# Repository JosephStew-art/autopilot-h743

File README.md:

STM32H743 autopilot board designed in KiCad. V2 routing is complete silkscreen cleanup remains.

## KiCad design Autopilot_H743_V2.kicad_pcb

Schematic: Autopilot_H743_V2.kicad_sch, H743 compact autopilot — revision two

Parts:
C1, C2: 33pF; Capacitor_SMD__C_0603_1608Metric; Rating 33pF / 100V C0G; MPN GCM1885C2A330JA16D; LCSC C126578
C3, C4, C8, C9, C10, C11, C12, C13, C14, C15, C16, C26, C29, C30, C32, C33, C35, C36, C39, C42, C43, C44, C45, C46: 100nF; C_0402_1005Metric; Rating 100nF / 16V X7R; MPN CL05B104KO5NNNC; LCSC C1525
C5, C6, C22, C34: 22uF; Capacitor_SMD__C_0805_2012Metric; Rating 22uF / 25V X5R; MPN CL21A226MAQNNNE; LCSC C45783
C7, C21, C38, C41: 10uF; Capacitor_SMD__C_0805_2012Metric; Rating 10uF / 35V X5R; MPN GRM21BR6YA106KE43L; LCSC C162422
C17, C28: 4.7uF; Capacitor_SMD__C_0603_1608Metric; Rating 4.7uF / 16V X5R; MPN CL10A475KO8NNNC; LCSC C19666
C18, C23, C24, C25, C27, C31, C37, C40: 1uF; Capacitor_SMD__C_0603_1608Metric; Rating 1uF / 50V X5R; MPN CL10A105KB8NNNC; LCSC C15849
C19, C20: 2.2uF; Capacitor_SMD__C_0603_1608Metric; Rating 2.2uF / 16V X5R; MPN CL10A225KO8NNNC; LCSC C23630
C47: 47uF; Capacitor_SMD__C_1206_3216Metric; Rating 47uF / 10V X5R; DC-bias derating applies; MPN CL31A476MPHNNNE; LCSC C96123
D1: RED; LED_SMD__LED_0603_1608Metric; Rating RED / status; MPN KT-0603R; LCSC C2286
F1: 1.5A hold; Fuse__Fuse_1812_4532Metric; Rating 1.5A hold / 16V; MPN SMD1812P150TF/16; LCSC C20810
J2: 5V BEC INPUT PADS; PowerInput_2Pad_4x4mm_P7mm; Rating Regulated 4.75-5.25 V; shared avionics 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
J3: TYPE-C-31-M-12; Connector_USB__USB_C_Receptacle_HRO_TYPE-C-31-M-12; Rating TYPE-C-31-M-12; MPN TYPE-C-31-M-12; LCSC C165948
J4: TF-01A / microSD; TF-01A; Rating TF-01A / microSD; MPN TF-01A; LCSC C91145
L1: 4.7uH; SRN6045; Rating 4.7uH / Irms3A / Isat4A; MPN SRN6045-4R7Y; LCSC C780210
Q1: AO3401A; Package_TO_SOT_SMD__SOT-23; Rating AO3401A; MPN AO3401A; LCSC C15127
Q2: MMBT3906 PNP; Package_TO_SOT_SMD__SOT-23; Rating MMBT3906 PNP; MPN MMBT3906 2A(RANGE:100-300); LCSC C2143
Q3: MMBT2222A NPN; Package_TO_SOT_SMD__SOT-23; Rating MMBT2222A NPN; MPN MMBT2222A 1P; LCSC C8512
R1, R2, R8, R12, R13, R17, R22, R23, R24, R38, R52, R59, R60, R61: 10k; R_0402_1005Metric; Rating 10k / 1% / 62.5mW; MPN 0402WGF1002TCE; LCSC C25744
R3, R57, R58: 1k; R_0402_1005Metric; Rating 1k / 1% / 62.5mW; MPN 0402WGF1001TCE; LCSC C11702
R4, R5, R14, R16, R20, R21, R62, R63, R64, R65, R66, R67, R68, R69, R71, R73, R75, R77, R79, R81, R83, R85: 100k; R_0402_1005Metric; Rating 100k / 1% / 62.5mW; MPN 0402WGF1003TCE; LCSC C25741
R6: 24k; R_0402_1005Metric; Rating 24k / 1% / 62.5mW; MPN 0402WGF2402TCE; LCSC C25769
R7: 470; R_0402_1005Metric; Rating 470 / 1% / 62.5mW; MPN 0402WGF4700TCE; LCSC C25117
R9, R10, R11: 300k; R_0402_1005Metric; Rating 300k / 1% / 62.5mW; MPN 0402WGF3003TCE; LCSC C25774
R15: 20k; R_0402_1005Metric; Rating 20k / 1% / 62.5mW; MPN 0402WGF2002TCE; LCSC C25765
R18, R19, R27, R28, R29, R30, R31, R32, R39, R40, R41, R42, R43, R44, R45, R46, R47, R48, R49, R50, R53, R54, R70, R72, R74, R76, R78, R80, R82, R84: 33; R_0402_1005Metric; Rating 33 / 1% / 62.5mW; MPN 0402WGF330JTCE; LCSC C25105
R25, R26, R55, R56: 4.7k; R_0402_1005Metric; Rating 4.7k / 1% / 62.5mW; MPN 0402WGF4701TCE; LCSC C25900
R33, R34, R35, R36, R37, R51: 49.9k; R_0402_1005Metric; Rating 49.9k / 1% / 62.5mW; MPN 0402WGF4992TCE; LCSC C25897
SW1: RESET; SW_TS-1088-AR02016; Rating RESET; MPN TS-1088-AR02016; LCSC C720477
SW2: BOOT; SW_TS-1088-AR02016; Rating BOOT; MPN TS-1088-AR02016; LCSC C720477
TP1, TP29: V3V3_CORE; SolderPad_D1.5mm; Rating V3V3_CORE
TP2: SWDIO; SolderPad_D1.2mm; Rating SWDIO
TP3: SWCLK; SolderPad_D1.2mm; Rating SWCLK
TP4, TP8, TP12, TP16, TP20, TP24, TP28, TP32, TP33, TP36, TP37, TP40, TP43, TP46, TP49, TP52, TP55, TP58: GND; SolderPad_D1.5mm; Rating GND
TP5, TP9, TP13, TP17, TP21, TP25: V5_PERIPH; SolderPad_D1.5mm; Rating V5_PERIPH
TP6: UART7_TX_EXT; SolderPad_D1.2mm; Rating UART7_TX_EXT
TP7: UART7_RX_EXT; SolderPad_D1.2mm; Rating UART7_RX_EXT
TP10: USART1_TX_EXT; SolderPad_D1.2mm; Rating USART1_TX_EXT
TP11: USART1_RX_EXT; SolderPad_D1.2mm; Rating USART1_RX_EXT
TP14: USART2_TX_EXT; SolderPad_D1.2mm; Rating USART2_TX_EXT
TP15: USART2_RX_EXT; SolderPad_D1.2mm; Rating USART2_RX_EXT
TP18: USART3_TX_EXT; SolderPad_D1.2mm; Rating USART3_TX_EXT
TP19: USART3_RX_EXT; SolderPad_D1.2mm; Rating USART3_RX_EXT
TP22: UART8_TX_EXT; SolderPad_D1.2mm; Rating UART8_TX_EXT
TP23: UART8_RX_EXT; SolderPad_D1.2mm; Rating UART8_RX_EXT
TP26: USART6_TX_EXT; SolderPad_D1.2mm; Rating USART6_TX_EXT
TP27: USART6_RX_EXT; SolderPad_D1.2mm; Rating USART6_RX_EXT
TP30: I2C1_SCL_EXT; SolderPad_D1.2mm; Rating I2C1_SCL_EXT
TP31: I2C1_SDA_EXT; SolderPad_D1.2mm; Rating I2C1_SDA_EXT
TP34: BATT_V_IN; SolderPad_D1.2mm; Rating BATT_V_IN
TP35: BATT_I_IN; SolderPad_D1.2mm; Rating BATT_I_IN
TP38, TP41, TP44, TP47, TP50, TP53, TP56, TP59: V5_MAIN_IN; SolderPad_D1.5mm; Rating V5_MAIN_IN
TP39: PWM1_OUT; SolderPad_D1.2mm; Rating PWM1_OUT
TP42: PWM2_OUT; SolderPad_D1.2mm; Rating PWM2_OUT
TP45: PWM3_OUT; SolderPad_D1.2mm; Rating PWM3_OUT
TP48: PWM4_OUT; SolderPad_D1.2mm; Rating PWM4_OUT
TP51: PWM5_OUT; SolderPad_D1.2mm; Rating PWM5_OUT
TP54: PWM6_OUT; SolderPad_D1.2mm; Rating PWM6_OUT
TP57: PWM7_OUT; SolderPad_D1.2mm; Rating PWM7_OUT
TP60: PWM8_OUT; SolderPad_D1.2mm; Rating PWM8_OUT
U1: STM32H743VIT6; Package_QFP__LQFP-100_14x14mm_P0.5mm; Rating STM32H743VIT6; MPN STM32H743VIT6; LCSC C114409
U2: AP63203WU-7; Package_TO_SOT_SMD__TSOT-23-6; Rating AP63203WU-7; MPN AP63203WU-7; LCSC C780769
U3: TPS2113APWR; Package_SO__TSSOP-8_4.4x3mm_P0.65mm; Rating TPS2113APWR; MPN TPS2113APWR; LCSC C130052
U4, U9: TPS7A2033PDBVR; Package_TO_SOT_SMD__SOT-23-5; Rating TPS7A2033PDBVR; MPN TPS7A2033PDBVR; LCSC C2862740
U5: TUSB320LIRWBR; Package_DFN_QFN__Texas_X2QFN-12_1.6x1.6mm_P0.4mm; Rating TUSB320LIRWBR; MPN TUSB320LIRWBR; LCSC C2836598
U6, U19: TPS2553DBVR; Package_TO_SOT_SMD__SOT-23-6; Rating TPS2553DBVR; MPN TPS2553DBVR; LCSC C55266
U7, U8, U13, U14, U15, U16, U17, U18, U20: USBLC6-2SC6; Package_TO_SOT_SMD__SOT-23-6; Rating USBLC6-2SC6; MPN USBLC6-2SC6; LCSC C7519
U10: BMI088; Package_LGA__Bosch_LGA-16_4.5x3mm_P0.5mm_LayoutBorder7x1y_C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; Rating BMI088; MPN BMI088; LCSC C194919
U11: MMC5983MA; Rating MMC5983MA; MPN MMC5983MA; LCSC C404329
U12: SPA06-003; Rating SPA06-003; MPN SPA06-003; LCSC C30589048
U21: SN74LV8T245PWR; Package_SO__TSSOP-20_4.4x6.5mm_P0.65mm; Rating SN74LV8T245PWR; MPN SN74LV8T245PWR; LCSC C20345798
U22, U23: TMUX1574PWR; Package_SO__TSSOP-16_4.4x5mm_P0.65mm; Rating TMUX1574PWR; MPN TMUX1574PWR; LCSC C2673443
Y1: 8MHz; Crystal__Crystal_SMD_5032-2Pin_5.0x3.2mm; Rating 8MHz / CL20pF; MPN X50328MSB2GI; LCSC C115962

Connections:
/ACTUATOR_OE_N: R59.2, U1.57 (PD10), U21.19 (OE_N), U22.15 (EN_N), U23.15 (EN_N)
/ADC_BATT_I: C43.1, R58.2, U1.16 (PC1)
/ADC_BATT_V: C42.1, R57.2, U1.15 (PC0)
/BATT_I_IN: R58.1, TP35.1
/BATT_V_IN: R57.1, TP34.1
/BOOT0: R2.1, SW2.2, U1.94 (BOOT0)
/BUCK_BST: C4.1, U2.6 (BST)
/BUCK_SW: C4.2, L1.1, U2.5 (SW)
/CC_HIGH_CURRENT_N: R12.2, R13.1, U5.7 (OUT1)
/CC_VBUS_DET: R11.2, U5.4 (VBUS_DET)
/CC_VBUS_R1: R9.2, R10.1
/CC_VBUS_R2: R10.2, R11.1
/GND: C1.2, C2.2, C3.2, C5.2, C6.2, C7.2, C8.2, C9.2, C10.2, C11.2, C12.2, C13.2, C14.2, C15.2, C16.2, C17.2, C18.2, C19.2, C20.2, C21.2, C22.2, C23.2, C24.2, C25.2, C26.2, C27.2, C28.2, C29.2, C30.2, C31.2, C32.2, C33.2, C34.2, C35.2, C36.2, C37.2, C38.2, C39.2, C40.2, C41.2, C42.2, C43.2, C44.2, C45.2, C46.2, C47.2, D1.1 (K), J2.1 (GND), J3.A1 (GND), J3.A12 (GND), J3.B1 (GND), J3.B12 (GND), J3.S1 (SHIELD), J4.6 (VSS), J4.10 (SHIELD), Q3.2 (E), R2.2, R4.2, R6.2, R7.2, R15.2, R16.2, R21.2, R51.2, R60.2, R61.2, R62.2, R63.2, R64.2, R65.2, R66.2, R67.2, R68.2, R69.2, R71.2, R73.2, R75.2, R77.2, R79.2, R81.2, R83.2, R85.2, SW1.2, TP4.1, TP8.1, TP12.1, TP16.1, TP20.1, TP24.1, TP28.1, TP32.1, TP33.1, TP36.1, TP37.1, TP40.1, TP43.1, TP46.1, TP49.1, TP52.1, TP55.1, TP58.1, U1.10 (VSS), U1.19 (VSSA), U1.26 (VSS), U1.49 (VSS), U1.74 (VSS), U1.99 (VSS), U2.4 (GND), U3.2 (EN_N), U3.5 (GND), U4.2 (GND), U5.3 (PORT), U5.10 (GND), U5.11 (EN_N), U6.2 (GND), U7.2 (GND), U8.2 (GND), U9.2 (GND), U10.2 (GNDA), U10.4 (GNDA), U10.6 (GNDIO), U10.7 (PS), U11.9 (GND), U11.11 (GND), U12.1 (GND), U12.5 (ADDR_I2C), U12.7 (GND), U13.2 (GND), U14.2 (GND), U15.2 (GND), U16.2 (GND), U17.2 (GND), U18.2 (GND), U19.2 (GND), U20.2 (GND), U21.10 (GND), U22.8 (GND), U23.8 (GND)
/HSE_IN: C1.1, U1.12 (PH0), Y1.1
/HSE_OUT: C2.1, U1.13 (PH1), Y1.2
/I2C1_SCL: R53.1, R55.2, U1.92 (PB6)
/I2C1_SCL_EXT: R53.2, TP30.1, U20.1 (I/O1), U20.6 (I/O1)
/I2C1_SDA: R54.1, R56.2, U1.93 (PB7)
/I2C1_SDA_EXT: R54.2, TP31.1, U20.3 (I/O2), U20.4 (I/O2)
/I2C2_SCL: R25.2, U1.46 (PB10), U11.1 (SCL), U12.4 (SCK)
/I2C2_SDA: R26.2, U1.47 (PB11), U11.16 (SDA), U12.3 (SDA)
/IMU_ACC_CS_N: R23.2, U1.9 (PC15), U10.14 (~CSB1)
/IMU_ACC_INT: U1.7 (PC13), U10.16 (INT1)
/IMU_GYR_CS_N: R24.2, U1.8 (PC14), U10.5 (~CSB2)
/IMU_GYR_INT: U1.1 (PE2), U10.12 (INT3)
/LED_STATUS_A: D1.2 (A), R3.2
/MAG_INT: U1.3 (PE4), U11.15 (INT)
/MAG_SETRESET_CAP: C34.1, U11.10 (CAP)
/MAIN_PMOS_GATE: Q1.1 (G), R4.1
/MAIN_VSNS: R5.2, R6.1, U3.3 (VSNS)
/MUX_ILIM: R7.1, U3.4 (ILIM)
/NRST: C3.1, R1.2, SW1.1, U1.14 (NRST)
/OTG_FS_DM: R19.2, U1.70 (PA11)
/OTG_FS_DP: R18.2, U1.71 (PA12)
/OUT_BANK1_DSHOT: R60.1, U1.58 (PD11), U22.1 (SEL_DSHOT)
/OUT_BANK2_DSHOT: R61.1, U1.84 (PD3), U23.1 (SEL_DSHOT)
/PERIPH_FAULT_N: R52.2, U1.4 (PE5), U19.4 (FAULT_N)
/PERIPH_ILIM: R51.1, U19.5 (ILIM)
/PWM1_5V: U21.18 (B1), U22.2 (S1A_PWM5V)
/PWM1_MCU: R62.1, U1.22 (PA0), U21.2 (A1), U22.3 (S1B_DSHOT)
/PWM1_OUT: R70.2, R71.1, TP39.1
/PWM1_SELECTED: R70.1, U22.4 (D1)
/PWM2_5V: U21.17 (B2), U22.5 (S2A_PWM5V)
/PWM2_MCU: R63.1, U1.23 (PA1), U21.3 (A2), U22.6 (S2B_DSHOT)
/PWM2_OUT: R72.2, R73.1, TP42.1
/PWM2_SELECTED: R72.1, U22.7 (D2)
/PWM3_5V: U21.16 (B3), U22.11 (S3A_PWM5V)
/PWM3_MCU: R64.1, U1.24 (PA2), U21.4 (A3), U22.10 (S3B_DSHOT)
/PWM3_OUT: R74.2, R75.1, TP45.1
/PWM3_SELECTED: R74.1, U22.9 (D3)
/PWM4_5V: U21.15 (B4), U22.14 (S4A_PWM5V)
/PWM4_MCU: R65.1, U1.25 (PA3), U21.5 (A4), U22.13 (S4B_DSHOT)
/PWM4_OUT: R76.2, R77.1, TP48.1
/PWM4_SELECTED: R76.1, U22.12 (D4)
/PWM5_5V: U21.14 (B5), U23.2 (S1A_PWM5V)
/PWM5_MCU: R66.1, U1.59 (PD12), U21.6 (A5), U23.3 (S1B_DSHOT)
/PWM5_OUT: R78.2, R79.1, TP51.1
/PWM5_SELECTED: R78.1, U23.4 (D1)
/PWM6_5V: U21.13 (B6), U23.5 (S2A_PWM5V)
/PWM6_MCU: R67.1, U1.60 (PD13), U21.7 (A6), U23.6 (S2B_DSHOT)
/PWM6_OUT: R80.2, R81.1, TP54.1
/PWM6_SELECTED: R80.1, U23.7 (D2)
/PWM7_5V: U21.12 (B7), U23.11 (S3A_PWM5V)
/PWM7_MCU: R68.1, U1.61 (PD14), U21.8 (A7), U23.10 (S3B_DSHOT)
/PWM7_OUT: R82.2, R83.1, TP57.1
/PWM7_SELECTED: R82.1, U23.9 (D3)
/PWM8_5V: U21.11 (B8), U23.14 (S4A_PWM5V)
/PWM8_MCU: R69.1, U1.62 (PD15), U21.9 (A8), U23.13 (S4B_DSHOT)
/PWM8_OUT: R84.2, R85.1, TP60.1
/PWM8_SELECTED: R84.1, U23.12 (D4)
/PWR_USB_SELECTED: R8.2, U1.96 (PB9), U3.1 (STAT)
/SDMMC1_CK: R32.1, U1.80 (PC12)
/SDMMC1_CMD: R31.1, U1.83 (PD2)
/SDMMC1_D0: R27.1, U1.65 (PC8)
/SDMMC1_D1: R28.1, U1.66 (PC9)
/SDMMC1_D2: R29.1, U1.78 (PC10)
/SDMMC1_D3: R30.1, U1.79 (PC11)
/SD_CLK_CARD: J4.5 (CLK), R32.2
/SD_CMD_CARD: J4.3 (CMD), R31.2, R37.2
/SD_D0_CARD: J4.7 (DAT0), R27.2, R33.2
/SD_D1_CARD: J4.8 (DAT1), R28.2, R34.2
/SD_D2_CARD: J4.1 (DAT2), R29.2, R35.2
/SD_D3_CARD: J4.2 (DAT3), R30.2, R36.2
/SD_DETECT_N: J4.9 (CD), R38.2, U1.95 (PB8)
/SPI1_MISO: U1.30 (PA6), U10.10 (SDO2), U10.15 (SDO1)
/SPI1_MOSI: U1.88 (PD7), U10.9 (SDI/SDA)
/SPI1_SCK: U1.29 (PA5), U10.8 (SCK/SCL)
/STATUS_LED: R3.1, U1.2 (PE3)
/SWCLK: TP3.1, U1.76 (PA14)
/SWDIO: TP2.1, U1.72 (PA13)
/UART7_RX: R40.2, U1.37 (PE7)
/UART7_RX_EXT: R40.1, TP7.1, U13.3 (I/O2), U13.4 (I/O2)
/UART7_TX: R39.1, U1.38 (PE8)
/UART7_TX_EXT: R39.2, TP6.1, U13.1 (I/O1), U13.6 (I/O1)
/UART8_RX: R48.2, U1.97 (PE0)
/UART8_RX_EXT: R48.1, TP23.1, U17.3 (I/O2), U17.4 (I/O2)
/UART8_TX: R47.1, U1.98 (PE1)
/UART8_TX_EXT: R47.2, TP22.1, U17.1 (I/O1), U17.6 (I/O1)
/USART1_RX: R42.2, U1.69 (PA10)
/USART1_RX_EXT: R42.1, TP11.1, U14.3 (I/O2), U14.4 (I/O2)
/USART1_TX: R41.1, U1.68 (PA9)
/USART1_TX_EXT: R41.2, TP10.1, U14.1 (I/O1), U14.6 (I/O1)
/USART2_RX: R44.2, U1.87 (PD6)
/USART2_RX_EXT: R44.1, TP15.1, U15.3 (I/O2), U15.4 (I/O2)
/USART2_TX: R43.1, U1.86 (PD5)
/USART2_TX_EXT: R43.2, TP14.1, U15.1 (I/O1), U15.6 (I/O1)
/USART3_RX: R46.2, U1.56 (PD9)
/USART3_RX_EXT: R46.1, TP19.1, U16.3 (I/O2), U16.4 (I/O2)
/USART3_TX: R45.1, U1.55 (PD8)
/USART3_TX_EXT: R45.2, TP18.1, U16.1 (I/O1), U16.6 (I/O1)
/USART6_RX: R50.2, U1.64 (PC7)
/USART6_RX_EXT: R50.1, TP27.1, U18.3 (I/O2), U18.4 (I/O2)
/USART6_TX: R49.1, U1.63 (PC6)
/USART6_TX_EXT: R49.2, TP26.1, U18.1 (I/O1), U18.6 (I/O1)
/USB_CC1: J3.A5 (CC1), U5.1 (CC1), U8.1 (I/O1), U8.6 (I/O1)
/USB_CC2: J3.B5 (CC2), U5.2 (CC2), U8.3 (I/O2), U8.4 (I/O2)
/USB_CONN_DM: J3.A7 (D-), J3.B7 (D-), R19.1, U7.3 (I/O2), U7.4 (I/O2)
/USB_CONN_DP: J3.A6 (D+), J3.B6 (D+), R18.1, U7.1 (I/O1), U7.6 (I/O1)
/USB_DETECT_BASE: Q3.1 (B), R20.2, R21.1
/USB_EN_PNP_BASE: Q2.1 (B), R13.2, R14.1
/USB_FAULT_N: R17.2, U1.5 (PE6), U6.4 (FAULT_N)
/USB_ILIM: R15.1, U6.5 (ILIM)
/USB_PRESENT_N: Q3.3 (C), R22.2, U1.32 (PC4)
/USB_PWR_EN: Q2.3 (C), R16.1, U6.3 (EN)
/USB_VBUS: C23.1, C26.1, J3.A4 (VBUS), J3.A9 (VBUS), J3.B4 (VBUS), J3.B9 (VBUS), R9.1, R20.1, U4.1 (IN), U4.3 (EN), U6.1 (IN), U7.5 (VBUS), U8.5 (VBUS)
/V3V3_CC: C24.1, Q2.2 (E), R12.1, R14.2, U4.5 (OUT_3V3), U5.12 (VDD)
/V3V3_CORE: C5.1, C6.1, C9.1, C10.1, C11.1, C12.1, C13.1, C14.1, C15.1, C16.1, C17.1, C18.1, C38.1, C39.1, J4.4 (VDD), L1.2, R1.1, R8.1, R17.1, R22.1, R33.1, R34.1, R35.1, R36.1, R37.1, R38.1, R52.1, R55.1, R56.1, R59.1, SW2.1, TP1.1, TP29.1, U1.6 (VBAT), U1.11 (VDD), U1.20 (VREF+), U1.21 (VDDA), U1.27 (VDD), U1.50 (VDD), U1.75 (VDD), U1.100 (VDD), U2.1 (FB), U13.5 (VBUS), U14.5 (VBUS), U15.5 (VBUS), U16.5 (VBUS), U17.5 (VBUS), U18.5 (VBUS), U20.5 (VBUS)
/V3V3_SENS: C28.1, C29.1, C30.1, C31.1, C32.1, C33.1, C35.1, C36.1, C37.1, R23.1, R24.1, R25.1, R26.1, U9.5 (OUT_3V3), U10.3 (VDD), U10.11 (VDDIO), U11.2 (VDD), U11.4 (CS_N), U11.13 (VDDIO), U12.2 (CSB), U12.6 (VDDIO), U12.8 (VDD)
/V5_MAIN_FUSED: F1.2, Q1.3 (D)
/V5_MAIN_IN: C47.1, F1.1, J2.2 (+5V), TP38.1, TP41.1, TP44.1, TP47.1, TP50.1, TP53.1, TP56.1, TP59.1
/V5_MAIN_PROT: C21.1, C40.1, Q1.2 (S), R5.1, U3.8 (IN1_MAIN), U19.1 (IN), U19.3 (EN)
/V5_PERIPH: C41.1, TP5.1, TP9.1, TP13.1, TP17.1, TP21.1, TP25.1, U19.6 (OUT)
/V5_SYS: C7.1, C8.1, C22.1, C27.1, C44.1, C45.1, C46.1, U2.2 (EN), U2.3 (IN), U3.7 (OUT), U9.1 (IN), U9.3 (EN), U21.1 (DIR_A_TO_B), U21.20 (VCC), U22.16 (VDD), U23.16 (VDD)
/V5_USB_LIMIT: C25.1, U3.6 (IN2_USB), U6.6 (OUT)
/VCAP_48: C19.1, U1.48 (VCAP)
/VCAP_73: C20.1, U1.73 (VCAP)

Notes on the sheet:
15 USART2 / 3.3V UART
Default-current USB hosts may not supply the complete board load.
TX/RX names are from the autopilot. V5_PERIPH shared across ports.
OUT 8
8MHz crystal: keep loop short. SWD 3V3 pad is a voltage reference. Hold BOOT, pulse RESET for ROM loader.
21 Output bank 2 / PWM or bidirectional DShot
OUT 1
OUT 4
pin 21
One physical STM32H743VIT6, original v1 symbol and pinout. C9–C16: 100nF per supply pin; place at the pin on PCB. NC crosses retain the intentionally unused v1 pins.
22 Servo power pads / electrical notes
No IMU heater. Place bypass at supply pins; keep buck heat away.
pin 50
OUT 2
No CLK pullup. 33Ω series resistors at MCU; bypass at card socket.
SEL low = 5V PWM; high = direct 3.3V DShot. OE high = disabled.
pin 11
USB data: route as a 90Ω differential pair; minimize stubs. ESD parts at connector. R18 / R19 near MCU. USB-C and bench-power behavior are retained from v1.
06 MCU clock / reset / boot / debug
19 Eight-channel 3.3V → 5V PWM buffer
03 3.3V buck regulator
16 USART3 / 3.3V UART
10 microSD / SDMMC
J2: pad 2 +5V, pad 1 GND. Regulated 4.75-5.25 V only. Servo feed branches BEFORE F1.
VREF+ / pin 20
14 USART1 / 3.3V UART
pin 6
07 USB-C connector / data and CC protection
18 USART6 / 3.3V UART
pin 75
CC_HIGH_CURRENT_N permits bench power when Type-C advertises 1.5A / 3A.
17 UART8 / 3.3V UART
09 Compass / barometer / I2C2 pullups
V5_MAIN_IN feeds servos directly from J2; USB powers avionics only. Servo current bypasses F1, Q1 and U3; no onboard servo fuse or reverse protection. Route +5V and GND with broad copper; size both for combined stall/startup current. Return servo current toward J2, away from sensor circuitry; use p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
12 External I2C / battery-monitor inputs
20 Output bank 1 / PWM or bidirectional DShot
OUT 7
OUT 3
DIR tied high: A→B. OE high disables buffer and both output selectors.
11 Peripheral 5V / USB-present detection

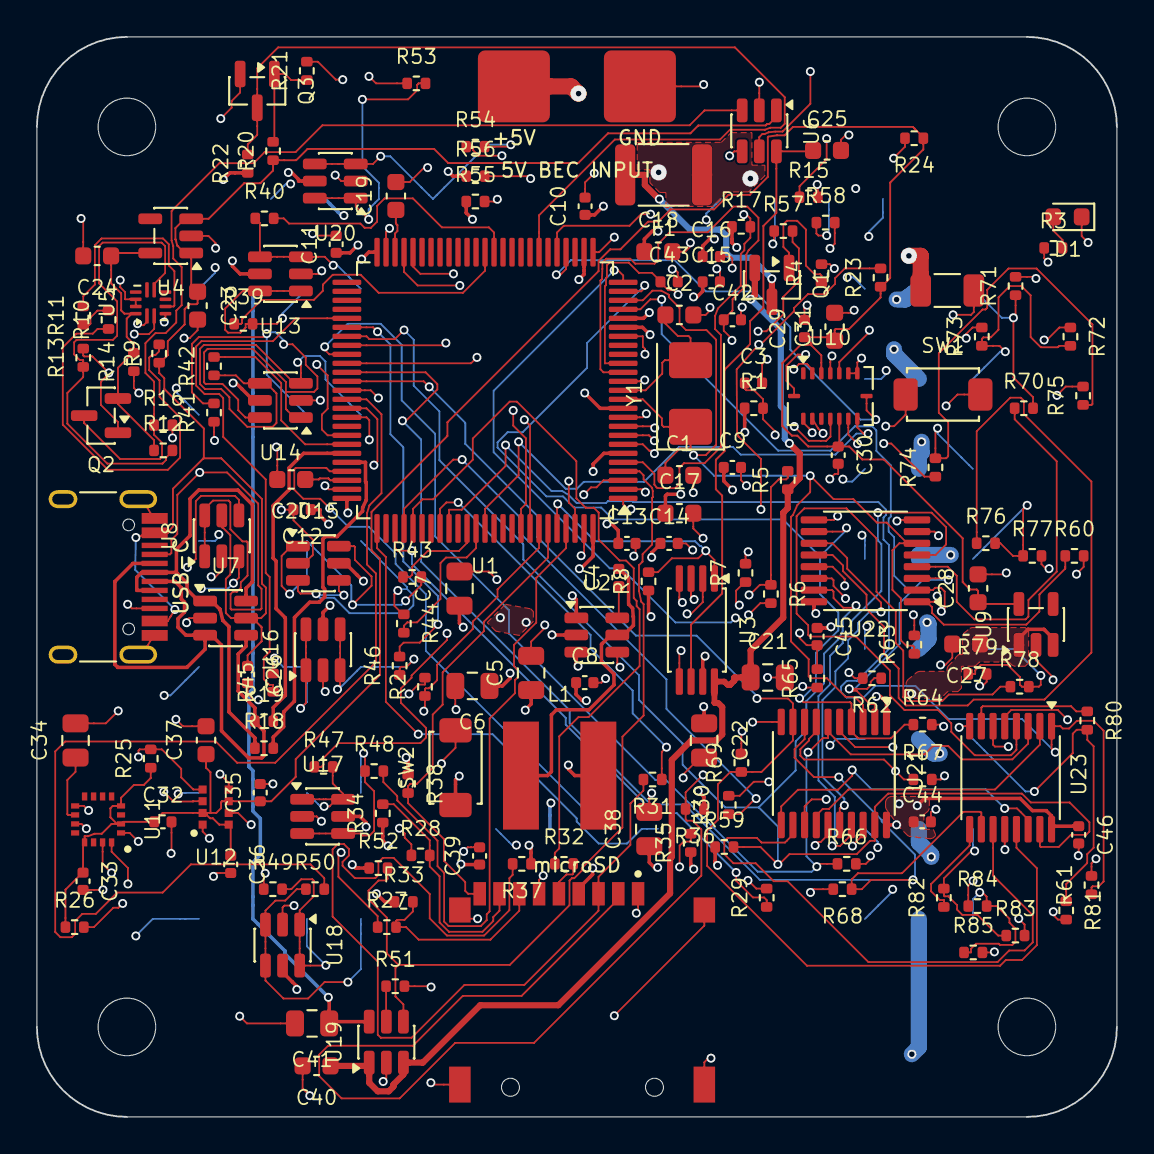
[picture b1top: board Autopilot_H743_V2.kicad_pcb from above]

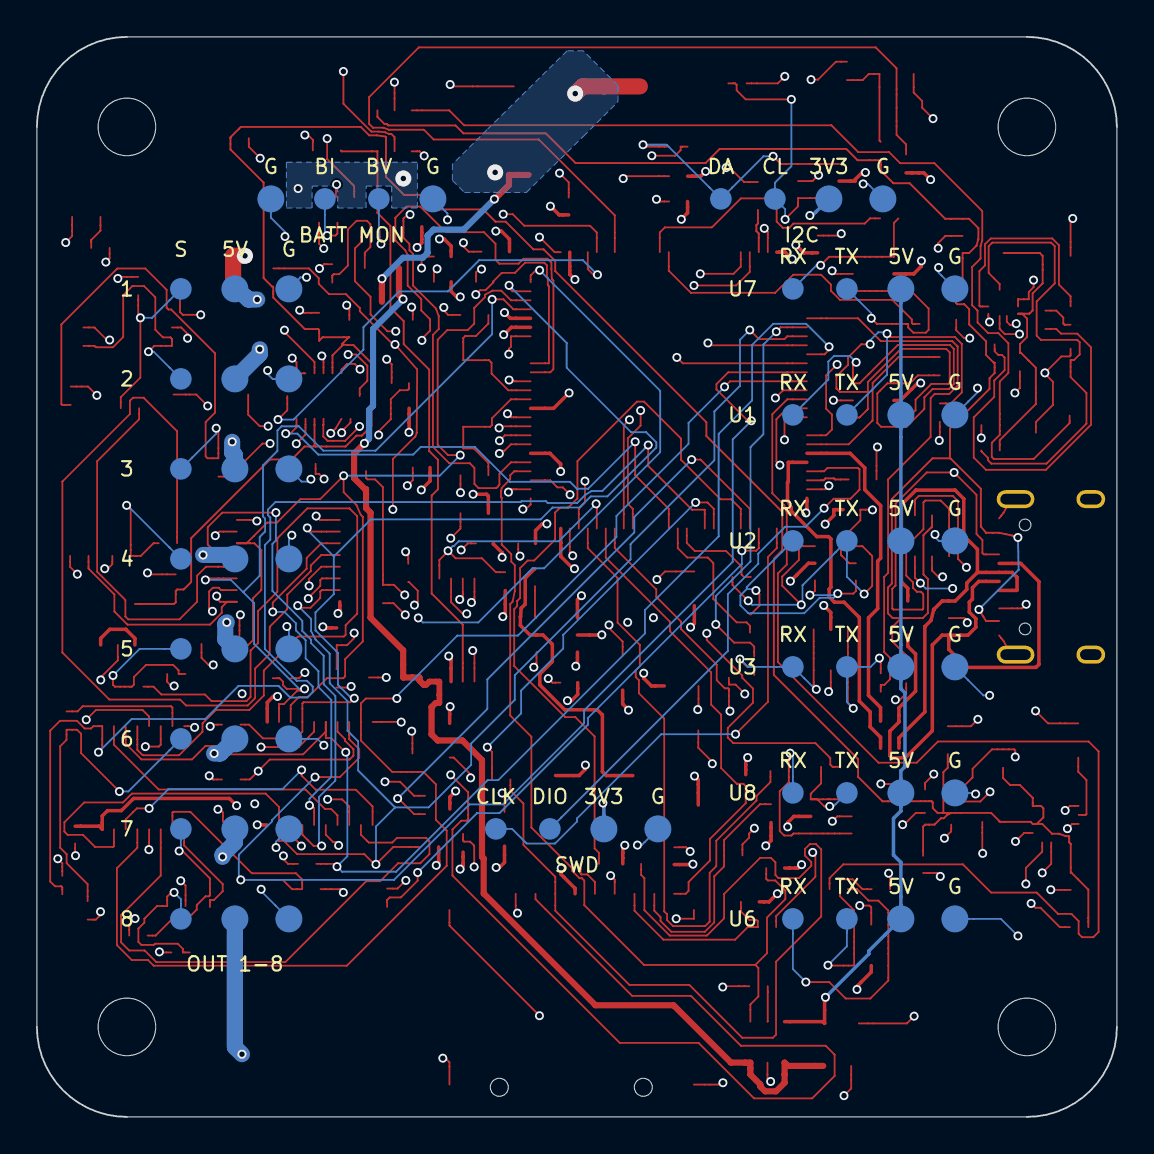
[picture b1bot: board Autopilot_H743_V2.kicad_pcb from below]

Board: 6 copper layers, 60.0 x 60.0 mm, 231 parts (60 on the bottom side), 136 nets.

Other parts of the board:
H1, H2, H3, H4: M3 / 50mm centres; MountingHole_3.2mm_M3
